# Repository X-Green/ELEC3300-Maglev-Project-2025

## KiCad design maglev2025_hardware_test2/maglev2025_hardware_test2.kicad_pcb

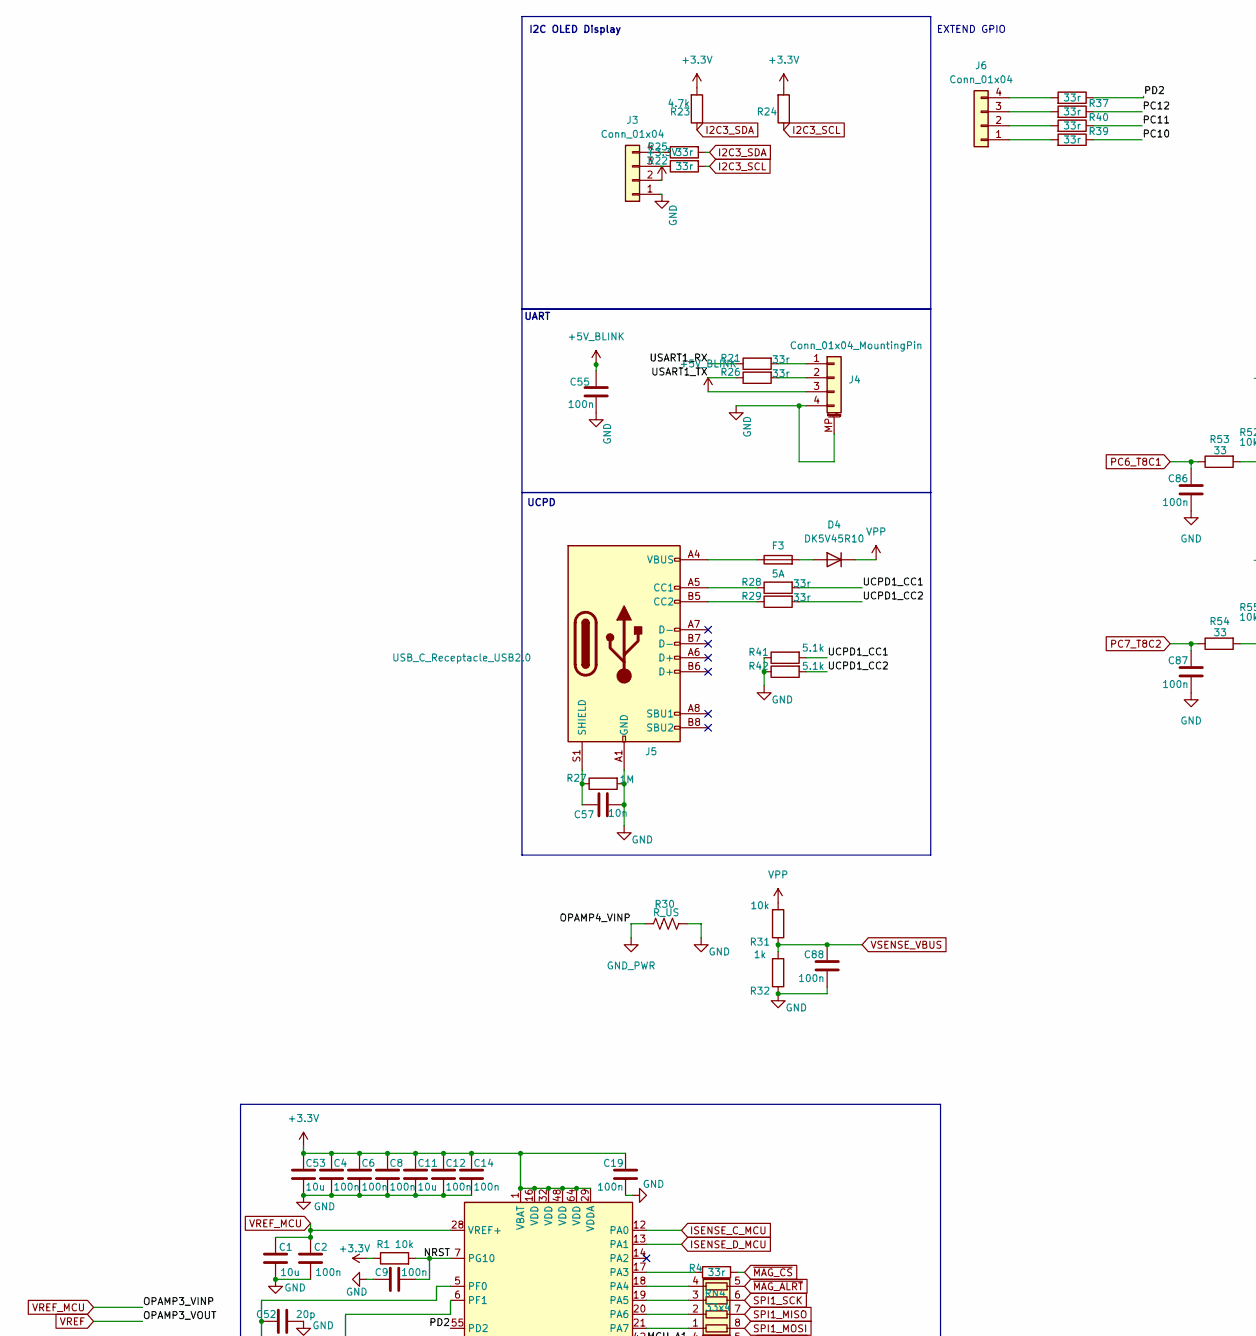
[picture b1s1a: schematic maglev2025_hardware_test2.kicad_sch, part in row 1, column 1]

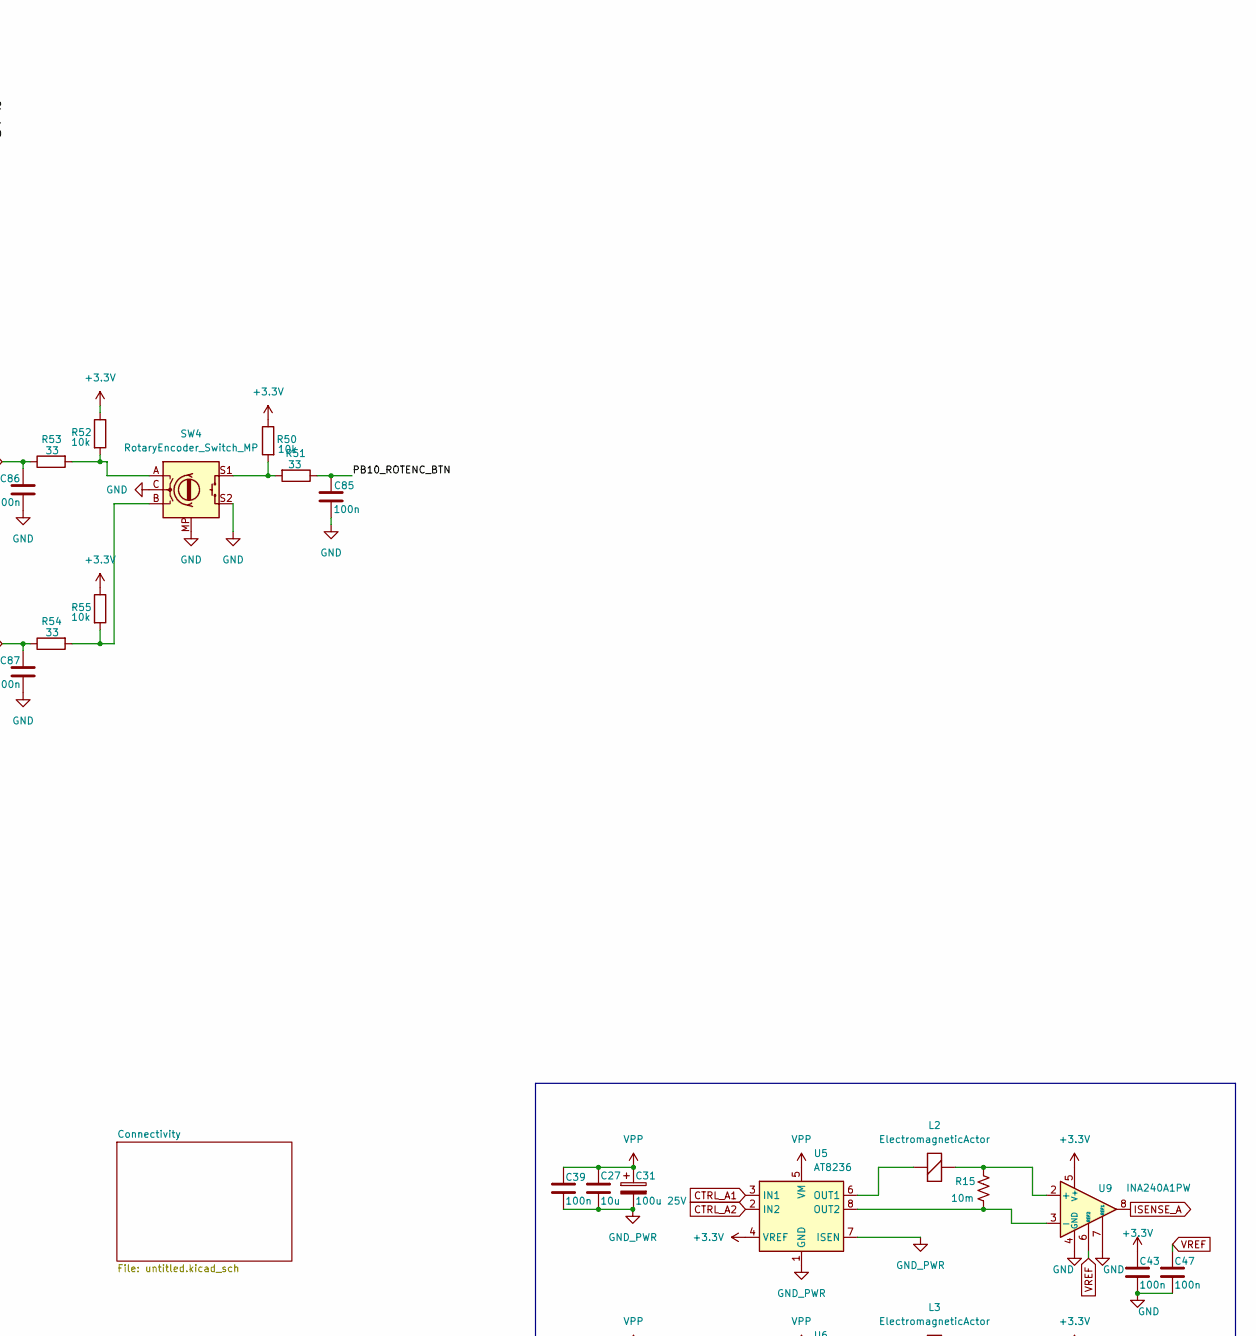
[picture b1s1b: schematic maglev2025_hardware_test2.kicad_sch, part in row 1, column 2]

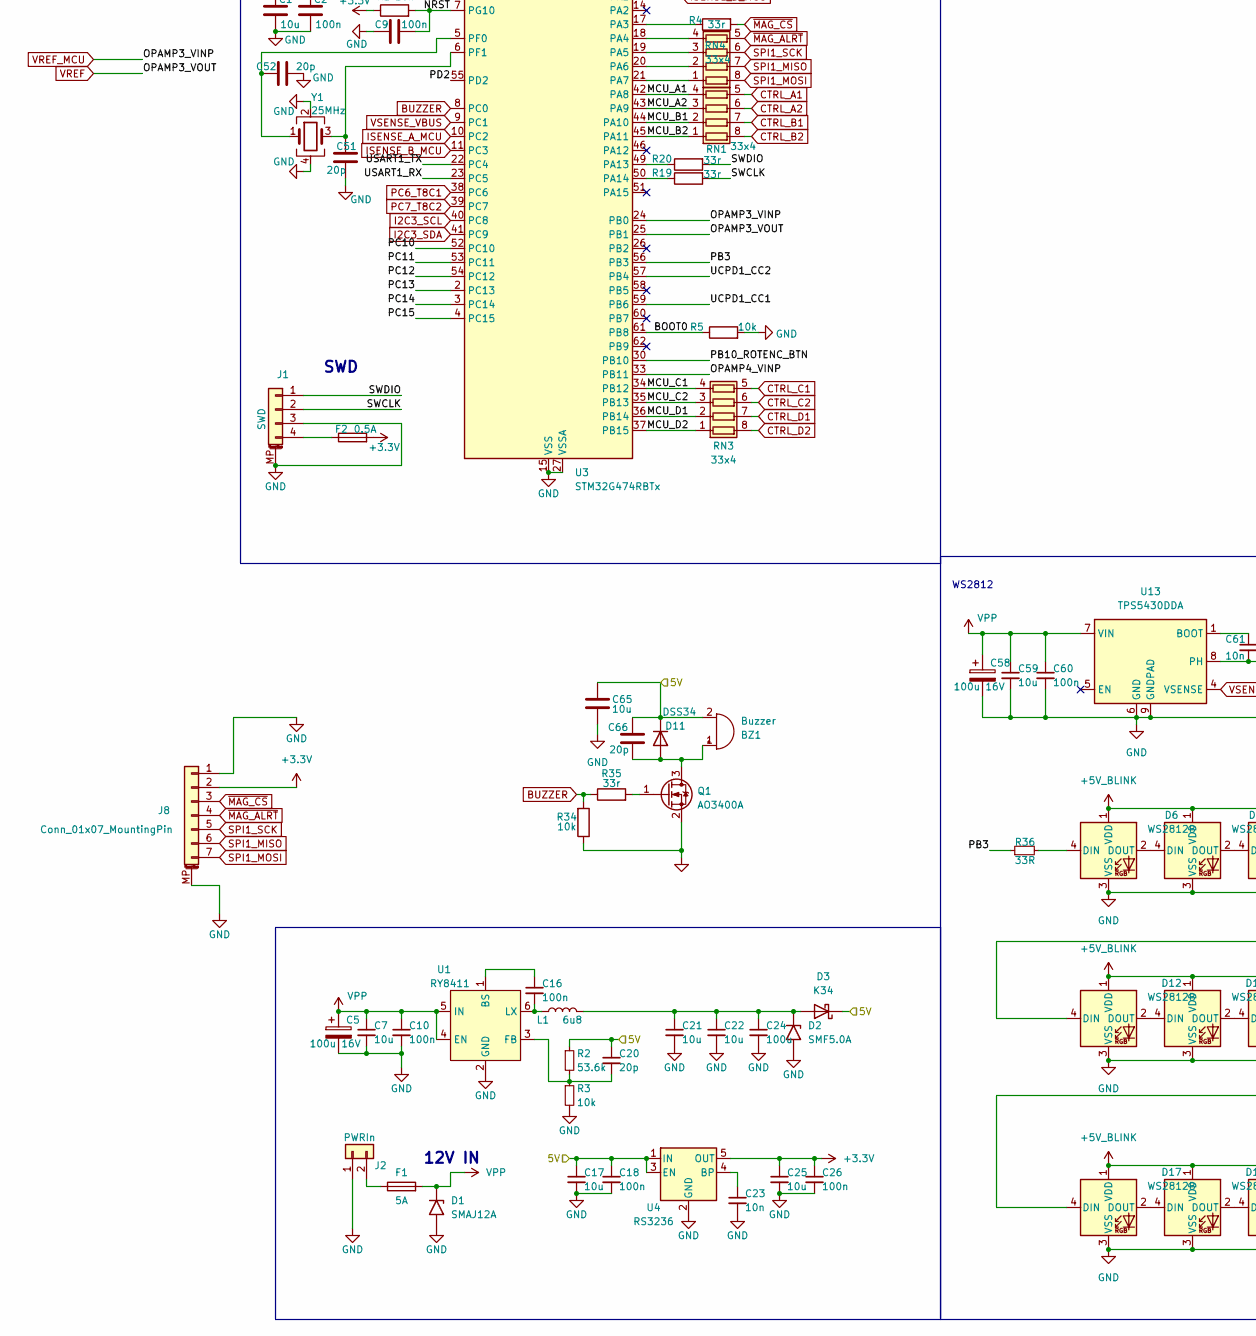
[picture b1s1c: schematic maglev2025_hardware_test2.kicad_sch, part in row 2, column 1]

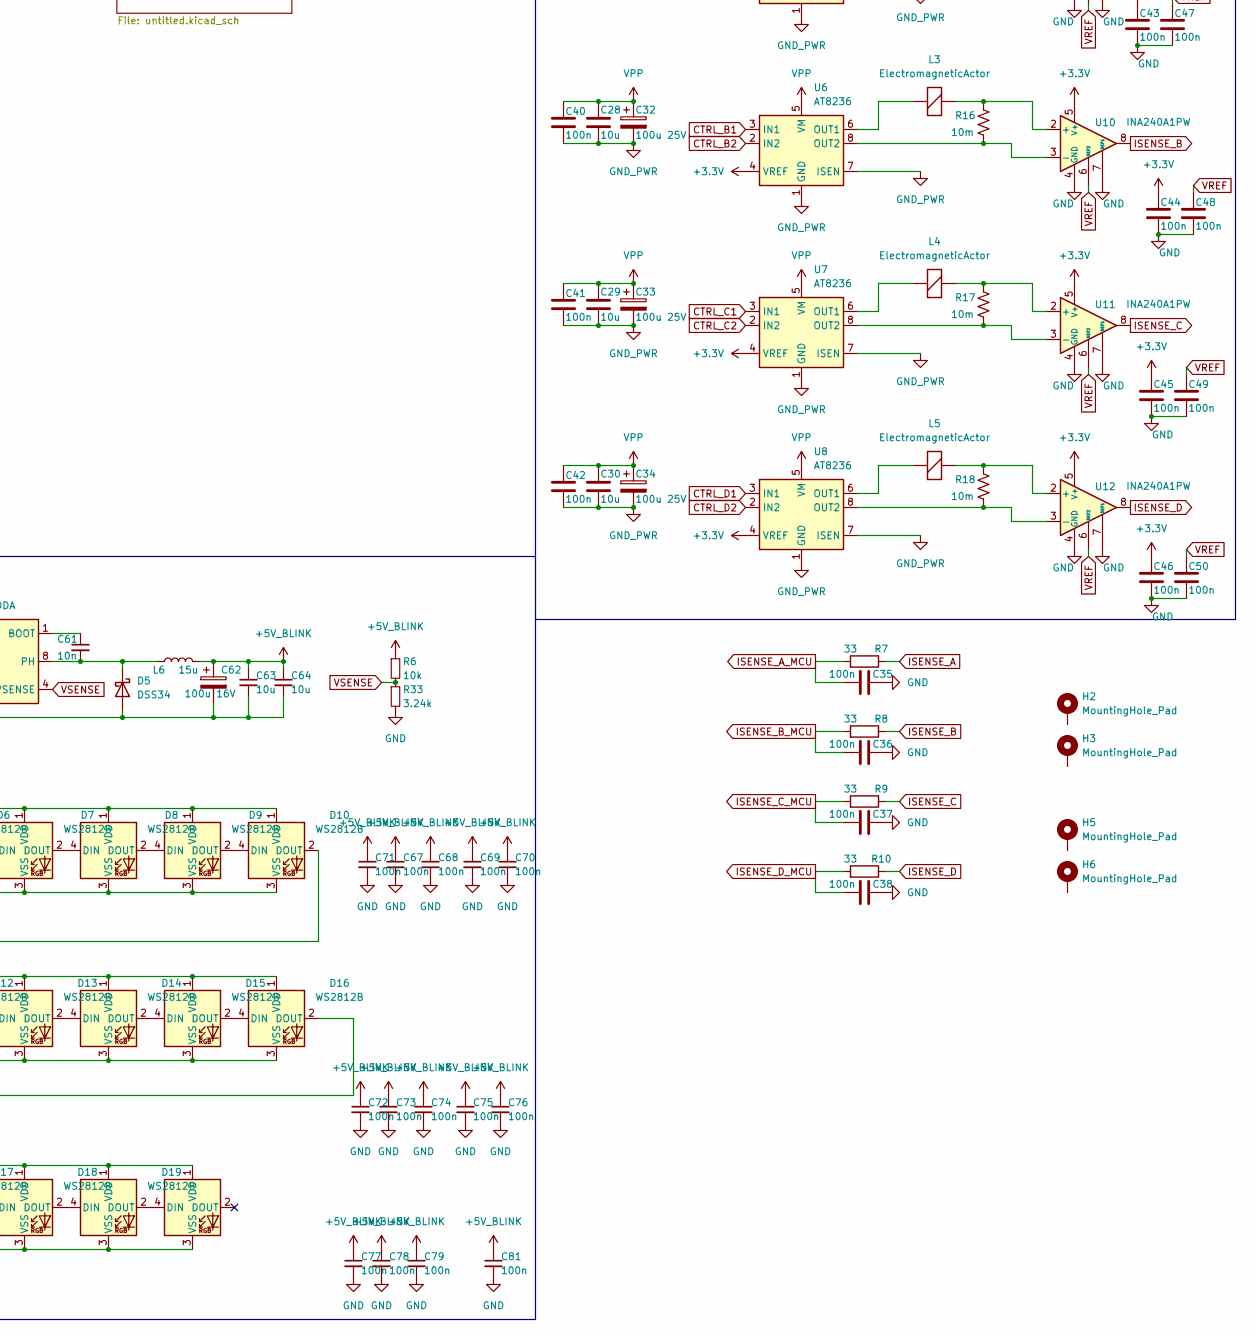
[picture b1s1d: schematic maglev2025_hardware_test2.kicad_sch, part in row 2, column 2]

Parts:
BZ1: Buzzer; MLT-9032
C1, C11, C17, C25, C53, C65: 10u; C_0603_1608Metric
C2, C4, C6, C8, C9, C10, C12, C14, C16, C18, C19, C26, C35, C36, C37, C38, C39, C40, C41, C42, C43, C44, C45, C46, C47, C48, C49, C50, C55, C60, C67, C68, C69, C70, C71, C72, C73, C74, C75, C76, C77, C78, C79, C81, C85, C86, C87, C88: 100n; C_0603_1608Metric
C5, C58, C62: 100u 16V; CP_Radial_D6.3mm_P2.50mm
C7, C21, C22, C27, C28, C29, C30, C59, C63, C64: 10u; C_1206_3216Metric
C20, C51, C52, C66: 20p; C_0603_1608Metric
C23, C57, C61: 10n; C_0603_1608Metric
C24: 100u; C_2220_5750Metric
C31, C32, C33, C34: 100u 25V; CP_Radial_D6.3mm_P2.50mm
D1: SMAJ12A; D_SMA
D2: SMF5.0A; D_SMF
D3: K34; D_SOD-123F
D4: DK5V45R10; D_PowerDI-5
D5: DSS34; D_SMA
D6, D7, D8, D9, D10, D12, D13, D14, D15, D16, D17, D18, D19, D20: WS2812B; LED_WS2812B_PLCC4_5.0x5.0mm_P3.2mm
D11: DSS34; D_SMF
F1, F3: 5A; Fuse_1206_3216Metric
F2: 0.5A; Fuse_1206_3216Metric
H2, H3, H5, H6: MountingHole_Pad; MountingHole_3.2mm_M3_DIN965_Pad_TopBottom
J1: SWD; Molex_PicoBlade_53261-0471_1x04-1MP_P1.25mm_Horizontal
J2: PWRIn; AMASS_XT30U-M_1x02_P5.0mm_Vertical
J3, J6: Conn_01x04; PinHeader_1x04_P2.54mm_Vertical
J4: Conn_01x04_MountingPin; JST_GH_BM04B-GHS-TBT_1x04-1MP_P1.25mm_Vertical
J5: USB_C_Receptacle_USB2.0; USB_C_Receptacle_HRO_TYPE-C-31-M-12
J8: Conn_01x07_MountingPin; JST_GH_SM07B-GHS-TB_1x07-1MP_P1.25mm_Horizontal
L1: 6u8; L_Sunlord_MWSA0402S
L2, L3, L4, L5: ElectromagneticActor; JST_PH_B2B-PH-K_1x02_P2.00mm_Vertical
L6: 15u; L_Chilisin_BMRx00060630
Q1: AO3400A; SOT-23
R1, R3, R5, R6, R31, R34, R50, R52, R55: 10k; R_0603_1608Metric
R2: 53.6k; R_0603_1608Metric
R4, R19, R20, R21, R22, R25, R26, R28, R29, R35, R37, R38, R39, R40: 33r; R_0603_1608Metric
R7, R8, R9, R10, R51, R53, R54: 33; R_0603_1608Metric
R15, R16, R17, R18: 10m; R_2512_6332Metric
R23, R24: 4.7k; R_0603_1608Metric
R27: 1M; R_0603_1608Metric
R30: R_US; R_2512_6332Metric
R32: 1k; R_0603_1608Metric
R33: 3.24k; R_0603_1608Metric
R36: 33R; R_0603_1608Metric
R41, R42: 5.1k; R_0603_1608Metric
RN1, RN3, RN4: 33x4; R_Array_Convex_4x0603
SW4: RotaryEncoder_Switch_MP; RotaryEncoder_Alps_EC11E-Switch_Vertical_H20mm_MountingHoles
U1: RY8411; SOT-23-6
U3: STM32G474RBTx; LQFP-64_10x10mm_P0.5mm
U4: RS3236; SOT-23-5
U5, U6, U7, U8: AT8236; Texas_HTSOP-8-1EP_3.9x4.9mm_P1.27mm_EP2.95x4.9mm_Mask2.4x3.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
U9, U10, U11, U12: INA240A1PW; TSSOP-8_4.4x3mm_P0.65mm
U13: TPS5430DDA; TI_SO-PowerPAD-8_ThermalVias
Y1: 25MHz; Crystal_SMD_3225-4Pin_3.2x2.5mm

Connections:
+3.3V: C4.1, C6.1, C8.1, C11.1, C12.1, C14.1, C19.1, C25.1, C26.1, C43.1, C44.1, C45.1, C46.1, C53.1, F2.2, J3.2, J8.2, R1.1, R23.2, R24.2, R50.1, R52.1, R55.1, U3.1 (VBAT), U3.16 (VDD), U3.29 (VDDA), U3.32 (VDD), U3.48 (VDD), U3.64 (VDD), U4.5 (OUT), U5.4 (VREF), U6.4 (VREF), U7.4 (VREF), U8.4 (VREF), U9.5 (V+), U10.5 (V+), U11.5 (V+), U12.5 (V+)
+5V_BLINK: C55.1, C62.1, C63.1, C64.1, C67.1, C68.1, C69.1, C70.1, C71.1, C72.1, C73.1, C74.1, C75.1, C76.1, C77.1, C78.1, C79.1, C81.1, D6.1 (VDD), D7.1 (VDD), D8.1 (VDD), D9.1 (VDD), D10.1 (VDD), D12.1 (VDD), D13.1 (VDD), D14.1 (VDD), D15.1 (VDD), D16.1 (VDD), D17.1 (VDD), D18.1 (VDD), D19.1 (VDD), D20.1 (VDD), J4.3, L6.2, R6.1
/5V: BZ1.2 (+), C17.1, C18.1, C20.1, C65.1, C66.1, D3.1 (K), D11.1 (K), R2.1, U4.1 (IN), U4.3 (EN)
/BOOT0: R5.1, U3.61 (PB8)
/MCU_A1: RN1.4 (R4.1), U3.42 (PA8)
/MCU_A2: RN1.3 (R3.1), U3.43 (PA9)
/MCU_B1: RN1.2 (R2.1), U3.44 (PA10)
/MCU_B2: RN1.1 (R1.1), U3.45 (PA11)
/MCU_C1: RN3.4 (R4.1), U3.34 (PB12)
/MCU_C2: RN3.3 (R3.1), U3.35 (PB13)
/MCU_D1: RN3.2 (R2.1), U3.36 (PB14)
/MCU_D2: RN3.1 (R1.1), U3.37 (PB15)
/NRST: C9.2, R1.2, U3.7 (PG10)
/PB3: R36.1, U3.56 (PB3)
/PB10_ROTENC_BTN: C85.2, R51.1, U3.30 (PB10)
/PC10: R38.1, U3.52 (PC10)
/PC11: R39.1, U3.53 (PC11)
/PC12: R40.1, U3.54 (PC12)
/PC13: U3.2 (PC13)
/PC14: U3.3 (PC14)
/PC15: U3.4 (PC15)
/PD2: R37.1, U3.55 (PD2)
/SWCLK: J1.2, R19.2
/SWDIO: J1.1, R20.2
/UCPD1_CC1: R28.2, R41.2, U3.59 (PB6)
/UCPD1_CC2: R29.2, R42.2, U3.57 (PB4)
/USART1_RX: R21.1, U3.23 (PC5)
/USART1_TX: R26.1, U3.22 (PC4)
BUZZER: R34.2, R35.1, U3.8 (PC0)
CTRL_A1: RN1.5 (R4.2), U5.3 (IN1)
CTRL_A2: RN1.6 (R3.2), U5.2 (IN2)
CTRL_B1: RN1.7 (R2.2), U6.3 (IN1)
CTRL_B2: RN1.8 (R1.2), U6.2 (IN2)
CTRL_C1: RN3.5 (R4.2), U7.3 (IN1)
CTRL_C2: RN3.6 (R3.2), U7.2 (IN2)
CTRL_D1: RN3.7 (R2.2), U8.3 (IN1)
CTRL_D2: RN3.8 (R1.2), U8.2 (IN2)
GND: C1.2, C2.2, C4.2, C5.2, C6.2, C7.2, C8.2, C9.1, C10.2, C11.2, C12.2, C14.2, C17.2, C18.2, C19.2, C21.2, C22.2, C23.2, C24.2, C25.2, C26.2, C35.1, C36.1, C37.1, C38.1, C43.2, C44.2, C45.2, C46.2, C47.2, C48.2, C49.2, C50.2, C51.2, C52.2, C53.2, C55.2, C57.2, C58.2, C59.2, C60.2, C62.2, C63.2, C64.2, C65.2, C67.2, C68.2, C69.2, C70.2, C71.2, C72.2, C73.2, C74.2, C75.2, C76.2, C77.2, C78.2, C79.2, C81.2, C85.1, C86.1, C87.1, C88.1, D1.2 (A2), D2.2 (A2), D5.2 (A), D6.3 (VSS), D7.3 (VSS), D8.3 (VSS), D9.3 (VSS), D10.3 (VSS), D12.3 (VSS), D13.3 (VSS), D14.3 (VSS), D15.3 (VSS), D16.3 (VSS), D17.3 (VSS), D18.3 (VSS), D19.3 (VSS), D20.3 (VSS), J1.3, J1.MP (MountPin), J2.1, J3.1, J4.4, J4.MP (MountPin), J5.A1 (GND), J5.A12 (GND), J5.B1 (GND), J5.B12 (GND), J8.1, J8.MP (MountPin), Q1.2 (S), R3.2, R5.2, R27.2, R30.2, R32.1, R33.2, R34.1, R41.1, R42.1, SW4.C, SW4.MP, SW4.S2, U1.2 (GND), U3.15 (VSS), U3.27 (VSSA), U3.31 (VSS), U3.47 (VSS), U3.63 (VSS), U4.2 (GND), U9.1 (GND), U9.4 (GND), U9.7 (REF1), U10.1 (GND), U10.4 (GND), U10.7 (REF1), U11.1 (GND), U11.4 (GND), U11.7 (REF1), U12.1 (GND), U12.4 (GND), U12.7 (REF1), U13.6 (GND), U13.9 (GNDPAD), Y1.2, Y1.4
GND_PWR: C27.2, C28.2, C29.2, C30.2, C31.2, C32.2, C33.2, C34.2, C39.2, C40.2, C41.2, C42.2, R30.1, U3.33 (PB11), U5.1 (GND), U5.7 (ISEN), U5.9 (GND), U6.1 (GND), U6.7 (ISEN), U6.9 (GND), U7.1 (GND), U7.7 (ISEN), U7.9 (GND), U8.1 (GND), U8.7 (ISEN), U8.9 (GND)
I2C3_SCL: R22.2, R24.1, U3.40 (PC8)
I2C3_SDA: R23.1, R25.2, U3.41 (PC9)
ISENSE_A: R7.1, U9.8
ISENSE_A_MCU: C35.2, R7.2, U3.10 (PC2)
ISENSE_B: R8.1, U10.8
ISENSE_B_MCU: C36.2, R8.2, U3.11 (PC3)
ISENSE_C: R9.1, U11.8
ISENSE_C_MCU: C37.2, R9.2, U3.12 (PA0)
ISENSE_D: R10.1, U12.8
ISENSE_D_MCU: C38.2, R10.2, U3.13 (PA1)
unnamed: BZ1.1 (-), C66.2, D11.2 (A), Q1.3 (D)
unnamed: C21.1, C22.1, C24.1, D2.1 (A1), D3.2 (A), L1.2
unnamed: D4.2 (A), F3.2
unnamed: C61.2, D5.1 (K), L6.1, U13.8 (PH)
unnamed: D6.4 (DIN), R36.2
unnamed: D6.2 (DOUT), D7.4 (DIN)
unnamed: D7.2 (DOUT), D8.4 (DIN)
unnamed: D8.2 (DOUT), D9.4 (DIN)
unnamed: D9.2 (DOUT), D10.4 (DIN)
unnamed: D10.2 (DOUT), D12.4 (DIN)
unnamed: D12.2 (DOUT), D13.4 (DIN)
unnamed: D13.2 (DOUT), D14.4 (DIN)
unnamed: D14.2 (DOUT), D15.4 (DIN)
unnamed: D15.2 (DOUT), D16.4 (DIN)
unnamed: D16.2 (DOUT), D17.4 (DIN)
unnamed: D17.2 (DOUT), D18.4 (DIN)
unnamed: D18.2 (DOUT), D19.4 (DIN)
unnamed: D19.2 (DOUT), D20.4 (DIN)
unnamed: F3.1, J5.A4 (VBUS), J5.A9 (VBUS), J5.B4 (VBUS), J5.B9 (VBUS)
unnamed: F2.1, J1.4
unnamed: F1.1, J2.2
unnamed: J3.3, R22.1
unnamed: J3.4, R25.1
unnamed: J4.1, R21.2
unnamed: J4.2, R26.2
unnamed: J5.A5 (CC1), R28.1
unnamed: J5.B5 (CC2), R29.1
unnamed: C57.1, J5.S1 (SHIELD), R27.1
unnamed: J6.1, R38.2
unnamed: J6.2, R39.2
unnamed: J6.3, R40.2
unnamed: J6.4, R37.2
unnamed: L2.2 (+), R15.1, U9.2 (+)
unnamed: L2.1 (-), U5.6 (OUT1)
unnamed: L3.2 (+), R16.1, U10.2 (+)
unnamed: L3.1 (-), U6.6 (OUT1)
unnamed: L4.2 (+), R17.1, U11.2 (+)
unnamed: L4.1 (-), U7.6 (OUT1)
unnamed: L5.2 (+), R18.1, U12.2 (+)
unnamed: L5.1 (-), U8.6 (OUT1)
unnamed: Q1.1 (G), R35.2
unnamed: R50.2, R51.2, SW4.S1
unnamed: R52.2, R53.2, SW4.A
unnamed: R54.2, R55.2, SW4.B
unnamed: RN4.1 (R1.1), U3.21 (PA7)
unnamed: RN4.2 (R2.1), U3.20 (PA6)
unnamed: RN4.3 (R3.1), U3.19 (PA5)
unnamed: RN4.4 (R4.1), U3.18 (PA4)
unnamed: C16.1, U1.1 (BS)
unnamed: C20.2, R2.2, R3.1, U1.3 (FB)
unnamed: C16.2, L1.1, U1.6 (LX)
unnamed: R4.1, U3.17 (PA3)
unnamed: R20.1, U3.49 (PA13)
unnamed: R19.1, U3.50 (PA14)
unnamed: C52.1, U3.5 (PF0), Y1.1
unnamed: C51.1, U3.6 (PF1), Y1.3
unnamed: C23.1, U4.4 (BP)
unnamed: R15.2, U5.8 (OUT2), U9.3 (-)
unnamed: R16.2, U6.8 (OUT2), U10.3 (-)
unnamed: R17.2, U7.8 (OUT2), U11.3 (-)
unnamed: R18.2, U8.8 (OUT2), U12.3 (-)
unnamed: C61.1, U13.1 (BOOT)
PC6_T8C1: C86.2, R53.1, U3.38 (PC6)
PC7_T8C2: C87.2, R54.1, U3.39 (PC7)
SPI1_MISO: J8.6, RN4.7 (R2.2)
SPI1_MOSI: J8.7, RN4.8 (R1.2)
SPI1_SCK: J8.5, RN4.6 (R3.2)
VPP: C5.1, C7.1, C10.1, C27.1, C28.1, C29.1, C30.1, C31.1, C32.1, C33.1, C34.1, C39.1, C40.1, C41.1, C42.1, C58.1, C59.1, C60.1, D1.1 (A1), D4.1 (K), F1.2, R31.2, U1.4 (EN), U1.5 (IN), U5.5 (VM), U6.5 (VM), U7.5 (VM), U8.5 (VM), U13.7 (VIN)
VREF: C47.1, C48.1, C49.1, C50.1, U3.25 (PB1), U9.6 (REF2), U10.6 (REF2), U11.6 (REF2), U12.6 (REF2)
VREF_MCU: C1.1, C2.1, U3.24 (PB0), U3.28 (VREF+)
VSENSE: R6.2, R33.1, U13.4 (VSENSE)
VSENSE_VBUS: C88.2, R31.1, R32.2, U3.9 (PC1)
~MAG_ALRT: J8.4, RN4.5 (R4.2)
~MAG_CS: J8.3, R4.2

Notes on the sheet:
12V IN
UCPD
UART
I2C OLED Display
SWD
EXTEND GPIO
WS2812

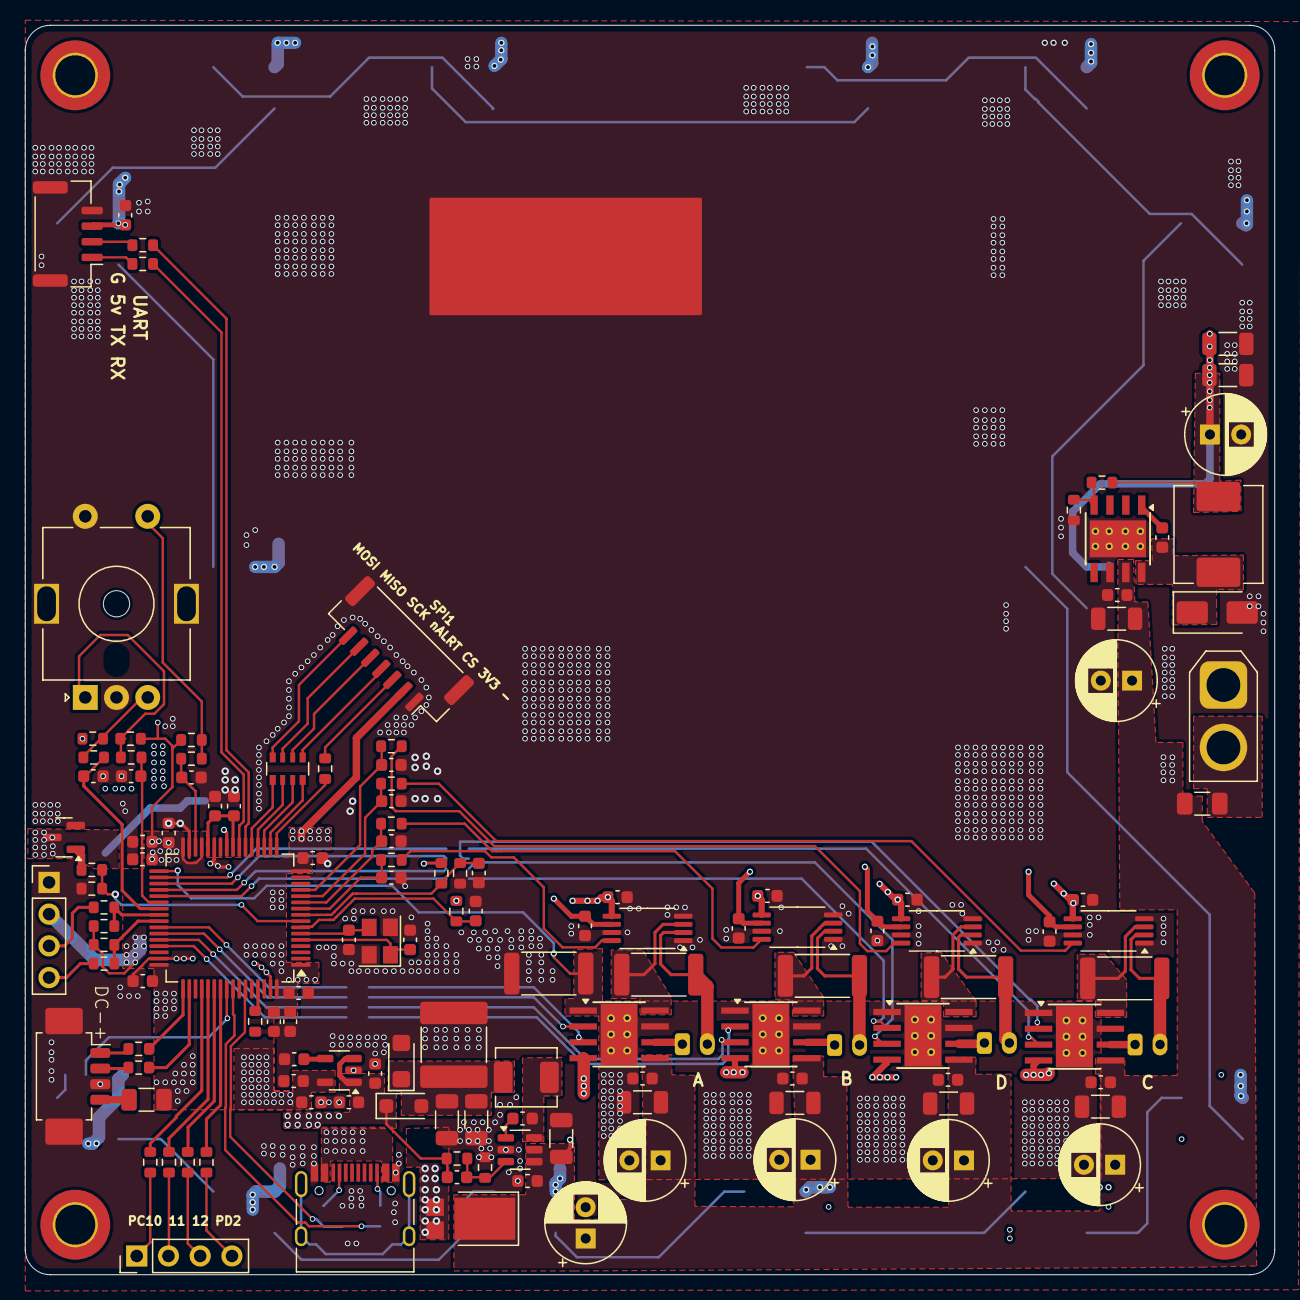
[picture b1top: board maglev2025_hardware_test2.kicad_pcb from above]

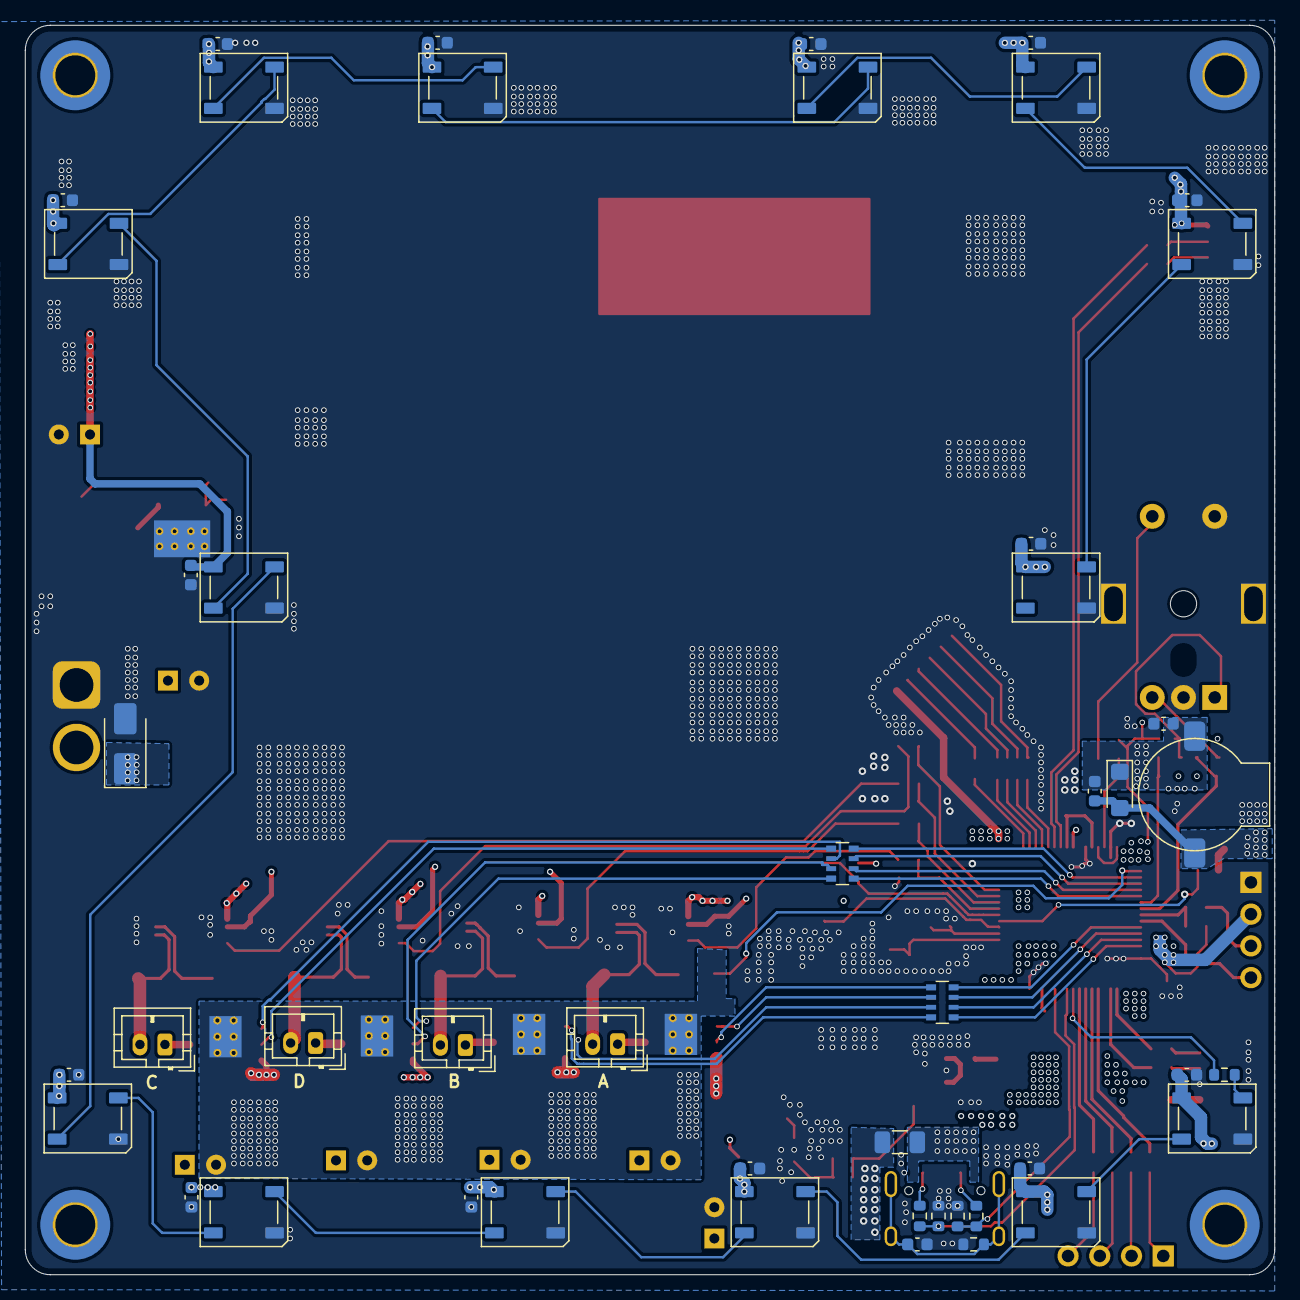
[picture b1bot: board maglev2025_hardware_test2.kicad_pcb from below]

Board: 4 copper layers, 100.0 x 100.0 mm, 182 parts (47 on the bottom side), 120 nets.

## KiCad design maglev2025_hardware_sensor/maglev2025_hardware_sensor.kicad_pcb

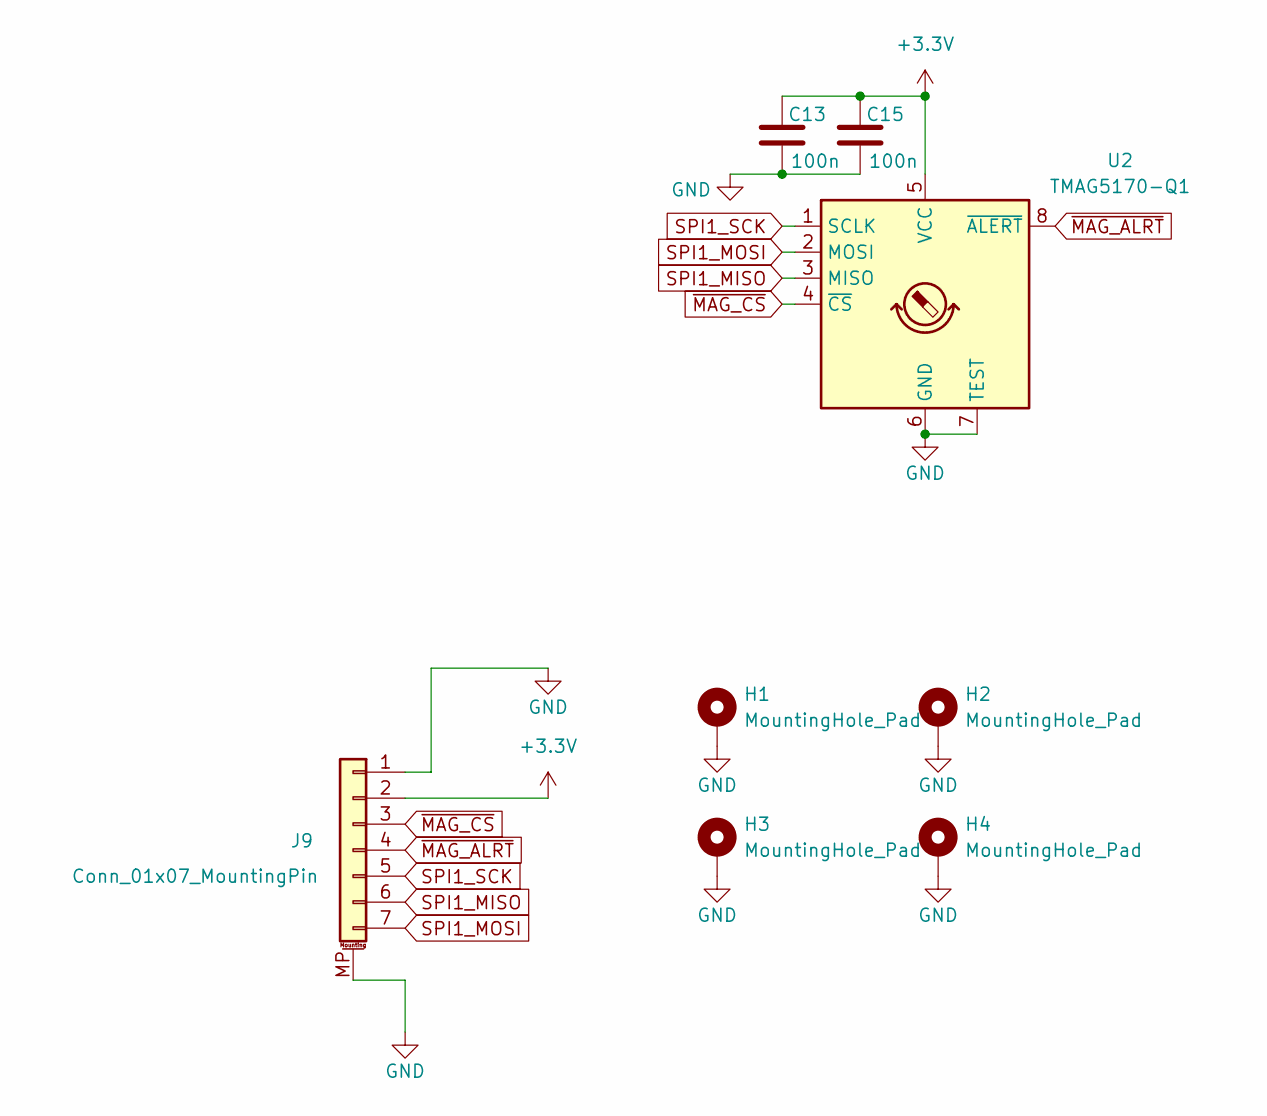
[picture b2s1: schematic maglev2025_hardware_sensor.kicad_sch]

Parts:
C13, C15: 100n; C_0603_1608Metric
H1, H2, H3, H4: MountingHole_Pad; MountingHole_2.2mm_M2_Pad_Via
J9: Conn_01x07_MountingPin; JST_GH_SM07B-GHS-TB_1x07-1MP_P1.25mm_Horizontal
U2: TMAG5170-Q1; VSSOP-8_3x3mm_P0.65mm

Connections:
+3.3V: C13.1, C15.1, J9.2, U2.5 (VCC)
GND: C13.2, C15.2, H1.1, H2.1, H3.1, H4.1, J9.1, J9.MP (MountPin), U2.6 (GND), U2.7 (TEST)
SPI1_MISO: J9.6, U2.3 (MISO)
SPI1_MOSI: J9.7, U2.2 (MOSI)
SPI1_SCK: J9.5, U2.1 (SCLK)
~MAG_ALRT: J9.4, U2.8 (~ALERT)
~MAG_CS: J9.3, U2.4 (~CS)

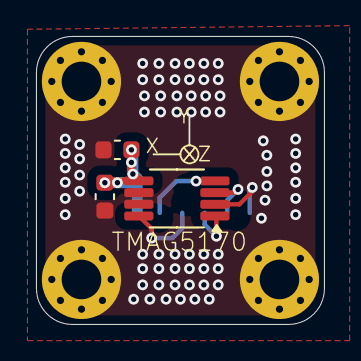
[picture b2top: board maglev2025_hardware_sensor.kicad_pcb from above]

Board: 2 copper layers, 16.0 x 16.0 mm, 8 parts (1 on the bottom side), 7 nets.

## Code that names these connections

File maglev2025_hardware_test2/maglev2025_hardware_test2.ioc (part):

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Mcu.Name=STM32G474R(B-C-E)Tx
Mcu.Package=LQFP64
Mcu.UserName=STM32G474RBTx
PA0.GPIOParameters=GPIO_Label
PA0.GPIO_Label=A2I1_IBSENSE
PA0.Mode=IN1-Single-Ended
PA0.Signal=ADC2_IN1
PA1.GPIOParameters=GPIO_Label
PA1.GPIO_Label=A2I2_IASENSE
PA1.Mode=IN2-Single-Ended
PA1.Signal=ADC2_IN2
PA10.Mode=Output_TB1TB2
PA10.Signal=HRTIM1_CHB1
PA11.Mode=Output_TB1TB2
PA11.Signal=HRTIM1_CHB2
PA13.Mode=Serial_Wire
PA13.Signal=SYS_JTMS-SWDIO
PA14.Mode=Serial_Wire
PA14.Signal=SYS_JTCK-SWCLK
PA3.GPIOParameters=GPIO_Label
PA3.GPIO_Label=SPI1_nCS
PA3.Signal=GPIO_Output
PA4.GPIOParameters=GPIO_Label
PA4.GPIO_Label=nMAG_ALRT
PA4.Signal=GPXTI4
PA5.Mode=Full_Duplex_Master
PA5.Signal=SPI1_SCK
PA6.Mode=Full_Duplex_Master
PA6.Signal=SPI1_MISO
PA7.Mode=Full_Duplex_Master
PA7.Signal=SPI1_MOSI
PA8.Mode=Output_TA1TA2
PA8.Signal=HRTIM1_CHA1
PA9.Mode=Output_TA1TA2
PA9.Signal=HRTIM1_CHA2
PB0.Mode=Follower
PB0.Signal=OPAMP3_VINP
PB1.Mode=Follower
PB1.Signal=OPAMP3_VOUT
PB10.Signal=GPXTI10
PB11.Mode=PGA_Internally_Connected
PB11.Signal=OPAMP4_VINP
PB12.Mode=Output_TC1TC2
PB12.Signal=HRTIM1_CHC1
PB13.Mode=Output_TC1TC2
PB13.Signal=HRTIM1_CHC2
PB14.Mode=Output_TD1TD2
PB14.Signal=HRTIM1_CHD1
PB15.Mode=Output_TD1TD2
PB15.Signal=HRTIM1_CHD2
PB3.Signal=S_TIM2_CH2
PB4.Mode=Sink_AllSignals
PB4.Signal=UCPD1_CC2
PB6.Mode=Sink_AllSignals
PB6.Signal=UCPD1_CC1
PB8-BOOT0.GPIOParameters=GPIO_Label
PB8-BOOT0.GPIO_Label=BOOT0
PB8-BOOT0.Signal=GPIO_Input
PC0.Signal=S_TIM1_CH1
PC1.GPIOParameters=GPIO_Label
PC1.GPIO_Label=A1I7_VBUS
PC1.Mode=IN7-Single-Ended
PC1.Signal=ADC1_IN7
PC10.Signal=GPIO_Output
PC11.Signal=GPIO_Output
PC12.Signal=S_TIM5_CH2
PC2.GPIOParameters=GPIO_Label
PC2.GPIO_Label=A2I8_IDSENSE
PC2.Mode=IN8-Single-Ended
PC2.Signal=ADC2_IN8
PC3.GPIOParameters=GPIO_Label
PC3.GPIO_Label=A2I9_ICSENSE
PC3.Mode=IN9-Single-Ended
PC3.Signal=ADC2_IN9
PC4.Mode=Asynchronous
PC4.Signal=USART1_TX
PC5.Mode=Asynchronous
PC5.Signal=USART1_RX
PC6.Signal=S_TIM8_CH1
PC7.Signal=S_TIM8_CH2
PC8.Mode=I2C
PC8.Signal=I2C3_SCL
PC9.Mode=I2C
PC9.Signal=I2C3_SDA
PD2.Signal=GPIO_Output
PF0-OSC_IN.Mode=HSE-External-Oscillator
PF0-OSC_IN.Signal=RCC_OSC_IN
PF1-OSC_OUT.Mode=HSE-External-Oscillator
PF1-OSC_OUT.Signal=RCC_OSC_OUT
RCC.HSE_VALUE=12000000
RCC.SYSCLKFreq_VALUE=170000000
RCC.SYSCLKSource=RCC_SYSCLKSOURCE_PLLCLK
board=custom

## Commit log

2025-03-03 hardware init
2025-03-05 schemetic and pin assignment
2025-03-06 Update schematic and ioc
2025-03-06 Layout mostly done
2025-03-08 Layout routing done, checking test
2025-03-08 Almost Complete
2025-03-08 Update gitignore
2025-03-08 ver 0.1 sent to fabrication
2025-03-11 Initialized C++ Project; Configured Makefile; Include DSP library
2025-03-11 rm compile_commands.json
2025-03-11 update ignore
2025-03-11 Add clang tidy and clang format
2025-03-11 Add some structures
2025-03-11 power input states
2025-03-12 Copied some definitions of TMAG5170 from TI documents
2025-03-12 Renaming CoilManager
2025-03-12 CubeMX configuration progress
2025-03-12 Add some tasks
2025-03-12 Fix multi definition
2025-03-12 Updated cubemx ioc: add EXTI and HRTIM configs. Not yet completed
2025-03-12 Generated code
2025-03-12 Use TIM17 as us delay source
2025-03-16 Update PCB for soldering; Fix schematic bug (SWD Pin)
2025-03-16 Adjust ioc: RCC 12MHz, VRef 2.90V; Regenerated Code
2025-03-16 Modify HRTIM and ADC triggering; Generated Code; Should work
2025-03-17 change ioc
2025-03-18 fixed, can compile successfully
2025-03-19 debug spi
2025-03-20 winwinwin, sensor can read
2025-04-07 Update cubemx and regenerated
2025-04-08 Setup Interrupt handlers
2025-04-08 Add some coil logics; naming change
2025-04-08 Format change and add PositionControl file
2025-04-08 Fix arm_math compiling error
2025-04-08 Update clang format
2025-04-08 Add logic for DMA sequential read
2025-04-09 Fix bug on namespace and C extern
2025-04-09 Tweaks on hrtim
2025-04-09 Change SPI speed
2025-04-09 c code move out of namespace
2025-04-09 Just remembered that TIM16 is used for delay_us
2025-04-09 Add 1kHz timer; Add logging; Change sample rate of TMAG5170
2025-04-10 Successfully use DMA to read Mag Data........
2025-04-10 Minor change in arm_math import
2025-04-10 Move TMAG5170 Macro into individual header file for better understanding
2025-04-11 successfully output pwm
2025-04-11 Minor Changes
2025-04-11 Can read ADC from DMA; Slower HRTIM 2x into 42500Hz
2025-04-12 Don't use cassert, use assert_param from stm32hal
2025-04-12 CoilCurrentControl seems okay; Changed from INA240A4 to INA240A1, noise get a lot lot better
2025-04-12 Position Logic Test Pending
2025-04-14 init hardware test2
2025-04-16 finish test2 sche
2025-04-16 Fix on test 2 schematic
2025-04-18 start layout
2025-04-22 addjust layout
2025-04-22 change adc pin out
2025-04-22 finish wiring
2025-04-22 finish layout, checking in progress
2025-04-23 adding external hal connector
2025-04-23 finished hal sensor board
2025-04-24 modify layout
2025-04-24 solve merge problem
2025-05-02 Fix compilation error in linux
2025-05-02 Update code from cubemx; Just able to compile.
2025-05-02 config ADC and regenerate files
2025-05-02 Fix Makefile caused by CubeMX bug
2025-05-02 Add 2812 Driver
2025-05-02 Add RGB colors
2025-05-03 Init code of Rotary Encoder TIM8 Combined Mode
2025-05-03 Prepare UART Rx DMA setup; test pending
2025-05-03 Buzzer & IOC & uart DMA & Namespace
2025-05-03 Use struct in RGB
2025-05-03 Fix TIM17 Update IRQ so that only corresponding event will trigger callback
2025-05-04 Change dir name to LEGACY
2025-05-04 Modify Mag config: Range
2025-05-04 Old setup seems to be able to float
2025-05-05 Change PID class and param
2025-05-05 Config ADC and OPAMP in new setup
2025-05-05 Fix static void in header
2025-05-05 Fix RCC and GPIO for nAlart
2025-05-05 Buzzer, LED, Encoder, ErrorChecker
2025-05-05 Add music buzzer init
2025-05-05 adding oled
2025-05-06 Add 2812 patterns
2025-05-06 change adc1 sample time
2025-05-06 VBUS Error Detection
2025-05-06 adding u8g2 lib
2025-05-06 Change a little bit target XY
2025-05-06 Supress warning on u8g2 lib
2025-05-06 update ui master
2025-05-06 Try to use unblocking play buzzer
2025-05-07 bugs
2025-05-07 fix bugs
2025-05-07 finialized version
2025-05-10 Format Fix
2025-05-10 Error Checker Fix
